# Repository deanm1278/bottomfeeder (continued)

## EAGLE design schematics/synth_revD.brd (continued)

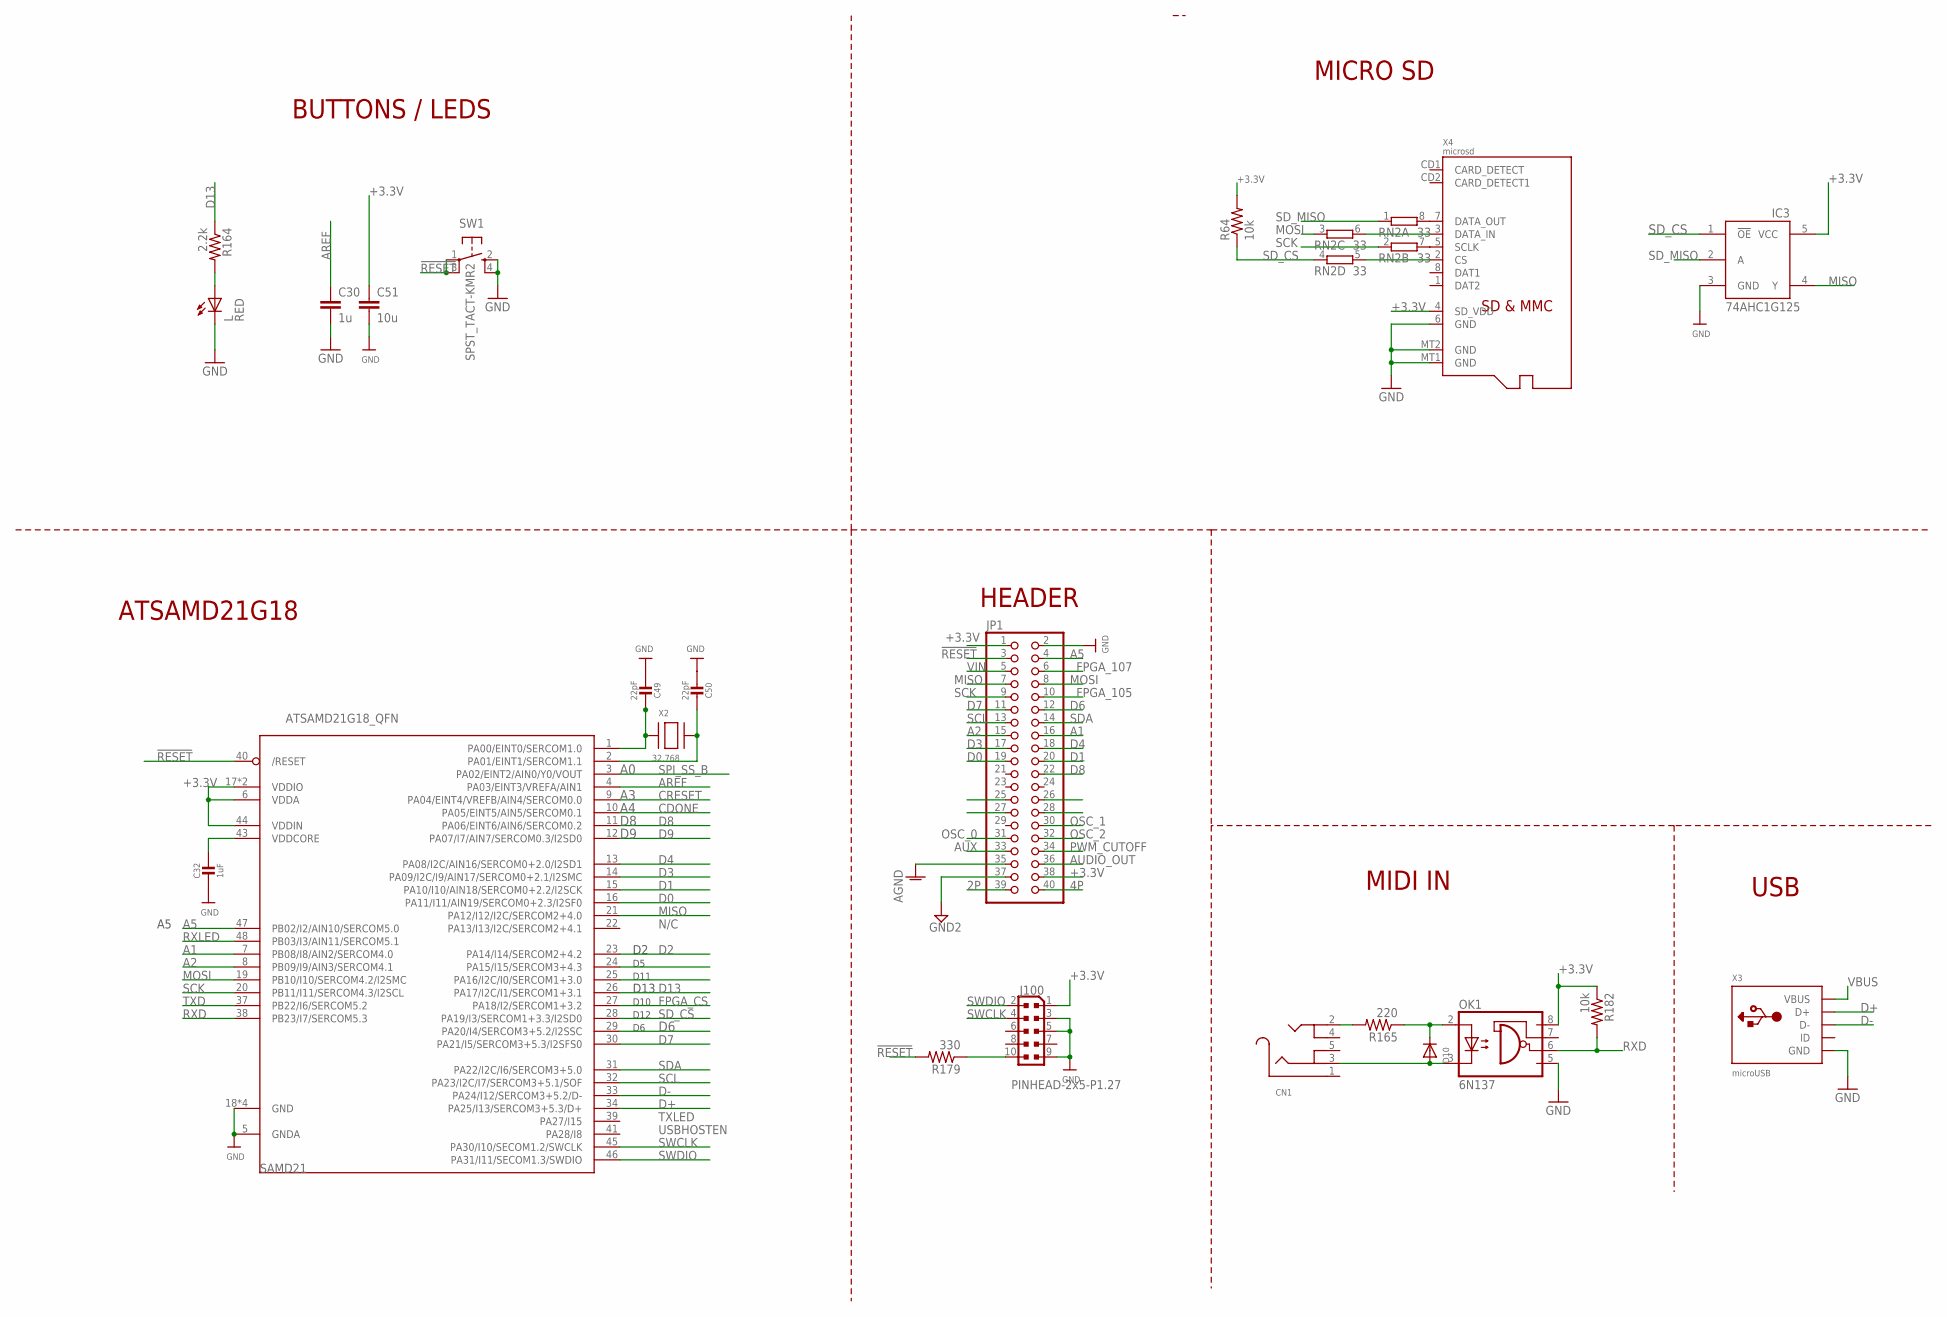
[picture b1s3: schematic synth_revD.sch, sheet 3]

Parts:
C30: 1u; C0603
C32: 1uF; 0603-NO
C49, C50: 22pF; 0603-NO
C51: 10u; C0603
CN1: AUDIO_3.5MMJACK; 4UCONN_19269
D10: DIODESOD-523; SOD-523
IC3: 74AHC1G125; SOT23-5L
J100: PINHEAD-2x5-P1.27; PINHEAD_2X05_127
JP1: PINHD-2X20; 2X20
L: RED; CHIP-LED0805
OK1: 6N137; DIL8-SMD
R64, R182: 10k; R0603
R164: 2.2k; R0603
R165: 220; R0603
R179: 330; R0603
RN2: 33; 0603-ARC
SAMD21: ATSAMD21G18_QFN; TQFN48_7MM
SW1: SPST_TACT-KMR2; KMR2
X2: 32.768; XTAL3215
X3: microUSB; 4UCONN_20329_V2
X4: microsd; MICROSD

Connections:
2P: JP1.39; also elsewhere on the board
4P: JP1.40; also elsewhere on the board
!RESET: JP1.3, R179.2, SAMD21.40 (/RESET), SW1.1, SW1.3 (P1)
+3.3V: C51.1, IC3.5 (VCC), J100.1, JP1.1, JP1.38, OK1.8 (VCC), R64.2, R182.1, SAMD21.6 (VDDA), SAMD21.17 (VDDIO), SAMD21.36 (VDDIO), SAMD21.44 (VDDIN), X4.4 (SD_VDD); also elsewhere on the board
A1: JP1.16, SAMD21.7 (PB08/I8/AIN2/SERCOM4.0)
A2: JP1.15, SAMD21.8 (PB09/I9/AIN3/SERCOM4.1)
A5: JP1.4, SAMD21.47 (PB02/I2/AIN10/SERCOM5.0)
AGND: JP1.35; also elsewhere on the board
AREF: C30.1, SAMD21.4 (PA03/EINT3/VREFA/AIN1)
AUDIO_OUT: JP1.36; also elsewhere on the board
AUX: JP1.33; also elsewhere on the board
CDONE: SAMD21.10 (PA05/EINT5/AIN5/SERCOM0.1); also elsewhere on the board
CRESET: SAMD21.9 (PA04/EINT4/VREFB/AIN4/SERCOM0.0); also elsewhere on the board
D0: JP1.19, SAMD21.16 (PA11/I11/AIN19/SERCOM0+2.3/I2SF0)
D1: JP1.20, SAMD21.15 (PA10/I10/AIN18/SERCOM0+2.2/I2SCK)
D2: SAMD21.23 (PA14/I14/SERCOM2+4.2)
D3: JP1.17, SAMD21.14 (PA09/I2C/I9/AIN17/SERCOM0+2.1/I2SMC)
D4: JP1.18, SAMD21.13 (PA08/I2C/AIN16/SERCOM0+2.0/I2SD1)
D6: JP1.12, SAMD21.29 (PA20/I4/SERCOM3+5.2/I2SSC)
D7: JP1.11, SAMD21.30 (PA21/I5/SERCOM3+5.3/I2SFS0)
D8: JP1.22, SAMD21.11 (PA06/EINT6/AIN6/SERCOM0.2)
D9: SAMD21.12 (PA07/I7/AIN7/SERCOM0.3/I2SD0)
D13: R164.1, SAMD21.26 (PA17/I2C/I1/SERCOM1+3.1)
D+: SAMD21.34 (PA25/I13/SERCOM3+5.3/D+), X3.D+
D-: SAMD21.33 (PA24/I12/SERCOM3+5.2/D-), X3.D-
FPGA_105: JP1.10; also elsewhere on the board
FPGA_107: JP1.6; also elsewhere on the board
FPGA_CS: SAMD21.27 (PA18/I2/SERCOM1+3.2); also elsewhere on the board
GND: C30.2, C32.2, C49.2, C50.2, C51.2, IC3.3 (GND), J100.3, J100.5, J100.9, JP1.2, L.C, OK1.5 (GND), SAMD21.5 (GNDA), SAMD21.18 (GND), SAMD21.35 (GND), SAMD21.42 (GND), SAMD21.THERMAL (GND), SW1.2 (S), SW1.4 (S1), X3.BASE@1 (GND), X3.BASE@2 (GND), X3.GND, X3.SPRT@1 (GND), X3.SPRT@2 (GND), X3.SPRT@3 (GND), X3.SPRT@4 (GND), X4.6 (GND), X4.MT1 (GND), X4.MT2 (GND); also elsewhere on the board
GND2: JP1.37; also elsewhere on the board
MISO: IC3.4 (Y), JP1.7, SAMD21.21 (PA12/I12/I2C/SERCOM2+4.0); also elsewhere on the board
MOSI: JP1.8, RN2.3 (1), SAMD21.19 (PB10/I10/SERCOM4.2/I2SMC); also elsewhere on the board
unnamed: CN1.2, R165.2
unnamed: J100.10, R179.1
unnamed: RN2.8 (2), X4.7 (DATA_OUT)
unnamed: RN2.7 (2), X4.5 (SCLK)
unnamed: RN2.6 (2), X4.3 (DATA_IN)
unnamed: RN2.5 (2), X4.2 (CS)
unnamed: L.A, R164.2
unnamed: C49.1, SAMD21.1 (PA00/EINT0/SERCOM1.0), X2.P$1
unnamed: C50.1, SAMD21.2 (PA01/EINT1/SERCOM1.1), X2.P$2
unnamed: D10.K (C), OK1.2 (A), R165.1
unnamed: CN1.3, D10.A, OK1.3 (C)
OSC_0: JP1.31; also elsewhere on the board
OSC_1: JP1.30; also elsewhere on the board
OSC_2: JP1.32; also elsewhere on the board
PWM_CUTOFF: JP1.34; also elsewhere on the board
RXD: OK1.6 (VO), R182.2, SAMD21.38 (PB23/I7/SERCOM5.3)
RXLED: SAMD21.48 (PB03/I3/AIN11/SERCOM5.1)
SCK: JP1.9, RN2.2 (1), SAMD21.20 (PB11/I11/SERCOM4.3/I2SCL); also elsewhere on the board
SCL: JP1.13, SAMD21.32 (PA23/I2C/I7/SERCOM3+5.1/SOF)
SDA: JP1.14, SAMD21.31 (PA22/I2C/I6/SERCOM3+5.0)
SD_CS: IC3.1 (!OE), R64.1, RN2.4 (1), SAMD21.28 (PA19/I3/SERCOM1+3.3/I2SD0)
SD_MISO: IC3.2 (A), RN2.1
SPI_SS_B: SAMD21.3 (PA02/EINT2/AIN0/Y0/VOUT); also elsewhere on the board
SWCLK: J100.4, SAMD21.45 (PA30/I10/SECOM1.2/SWCLK)
SWDIO: J100.2, SAMD21.46 (PA31/I11/SECOM1.3/SWDIO)
TXD: SAMD21.37 (PB22/I6/SERCOM5.2)
VBUS: X3.VBUS; also elsewhere on the board
VDDCORE1: C32.1, SAMD21.43 (VDDCORE)
VIN: JP1.5; also elsewhere on the board

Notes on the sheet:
N/C
TXLED
USBHOSTEN
RXLED
TXD
RXD
D12
D10
D11
D13
ATSAMD21G18
BUTTONS / LEDS
MICRO SD
USB
HEADER
MIDI IN

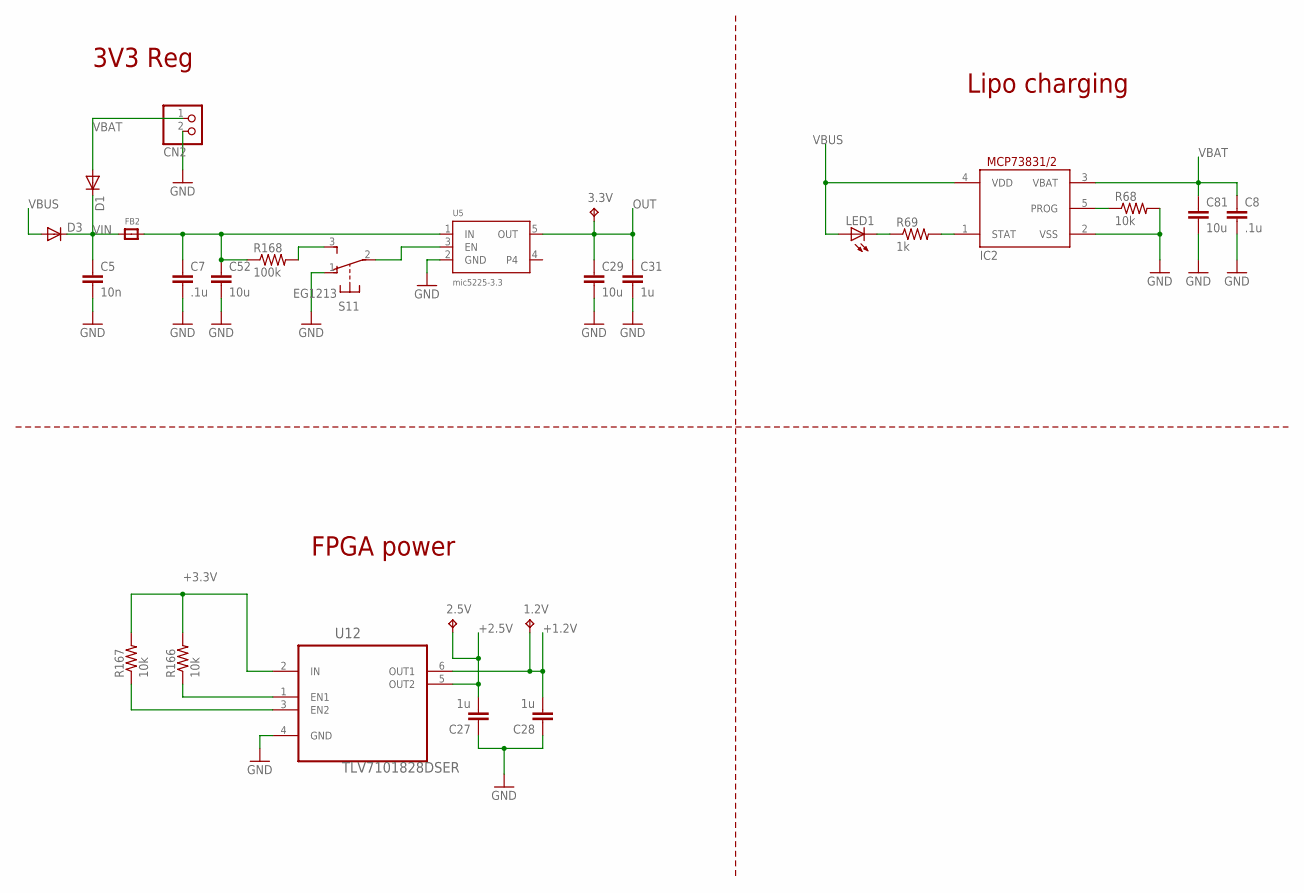
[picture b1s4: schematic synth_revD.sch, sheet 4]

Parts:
1.2V, 2.5V, 3.3V: TPB1,27; B1,27
C5: 10n; C0603
C7, C8: .1u; C0603
C27, C28, C31: 1u; C0603
C29, C52, C81: 10u; C0603
CN2: JST_2PIN-SMT-RA; JST-PH-2-SMT-RA
D1, D3: DIODE-SOD123; SOD123
FB2: FERRITE; 0603
IC2: MCP73831/OT; SOT23-5L
LED1: LEDCHIP-LED0805; CHIP-LED0805
R68, R166, R167: 10k; R0603
R69: 1k; R0603
R168: 100k; R0603
S1: EG1213
U5: mic5225-3.3; SOT23-5
U12: TLV7101828DSER; SON50P150X150X80-6N

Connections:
$P9999: C7.1, C52.1, FB2.2, R168.1, U5.1 (IN)
+1.2V: 1.2V.TP, C28.2, U12.6 (OUT1); also elsewhere on the board
+2.5V: 2.5V.TP, C27.2, U12.5 (OUT2)
+3.3V: R166.2, R167.2, U12.2 (IN); also elsewhere on the board
GND: C5.2, C7.2, C8.2, C27.1, C28.1, C29.2, C31.2, C52.2, C81.2, CN2.2 (1), IC2.2 (VSS), R68.2, S1.1 (O), U5.2 (GND), U12.4 (GND); also elsewhere on the board
unnamed: R168.2, S1.3 (S)
unnamed: IC2.5 (PROG), R68.1
unnamed: S1.2, U5.3 (EN)
unnamed: IC2.1 (STAT), R69.2
unnamed: LED1.C, R69.1
unnamed: R166.1, U12.1 (EN1)
unnamed: R167.1, U12.3 (EN2)
OUT: 3.3V.TP, C29.1, C31.1, U5.5 (OUT)
VBAT: C8.1, C81.1, CN2.1 (2), D1.A, IC2.3 (VBAT)
VBUS: D3.A, IC2.4 (VDD), LED1.A; also elsewhere on the board
VIN: C5.1, D1.C, D3.C, FB2.1; also elsewhere on the board

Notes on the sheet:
FPGA power
3V3 Reg
Lipo charging

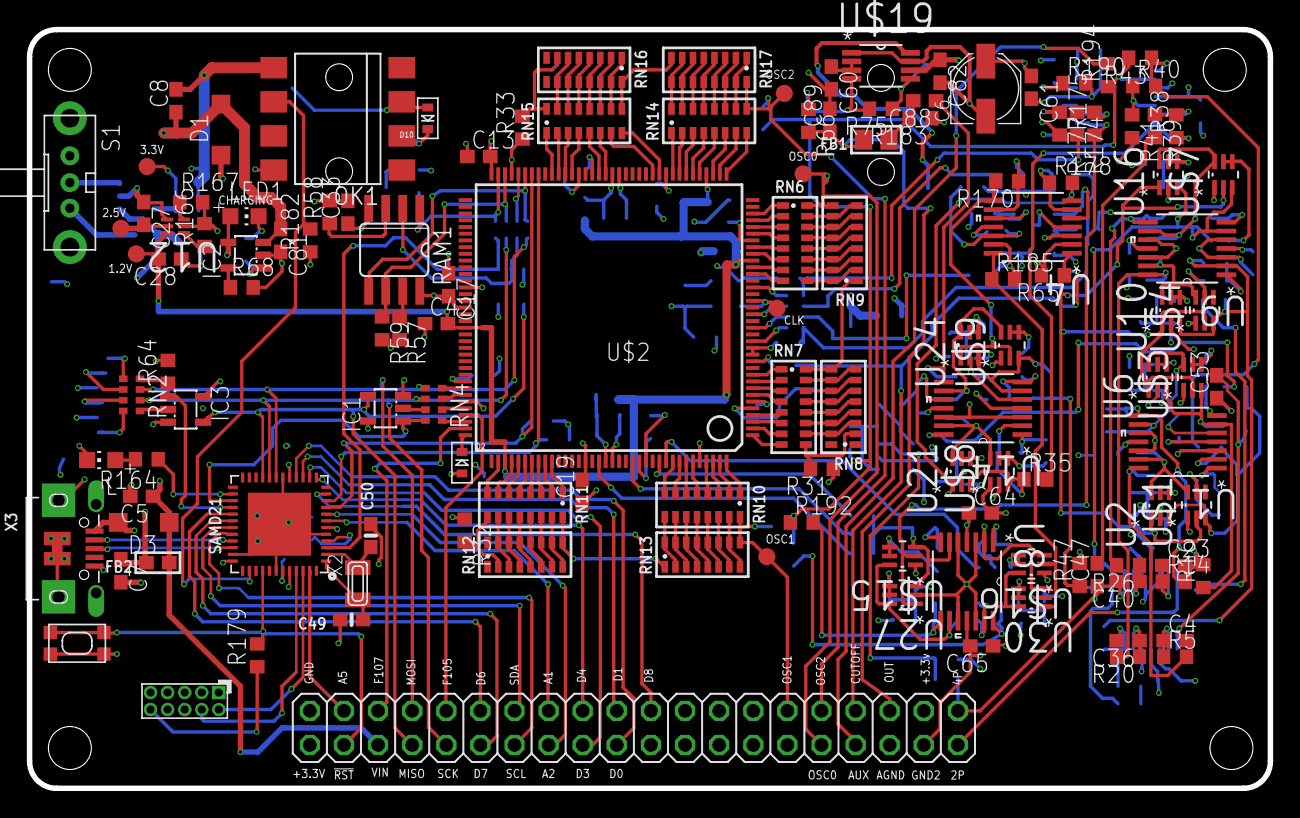
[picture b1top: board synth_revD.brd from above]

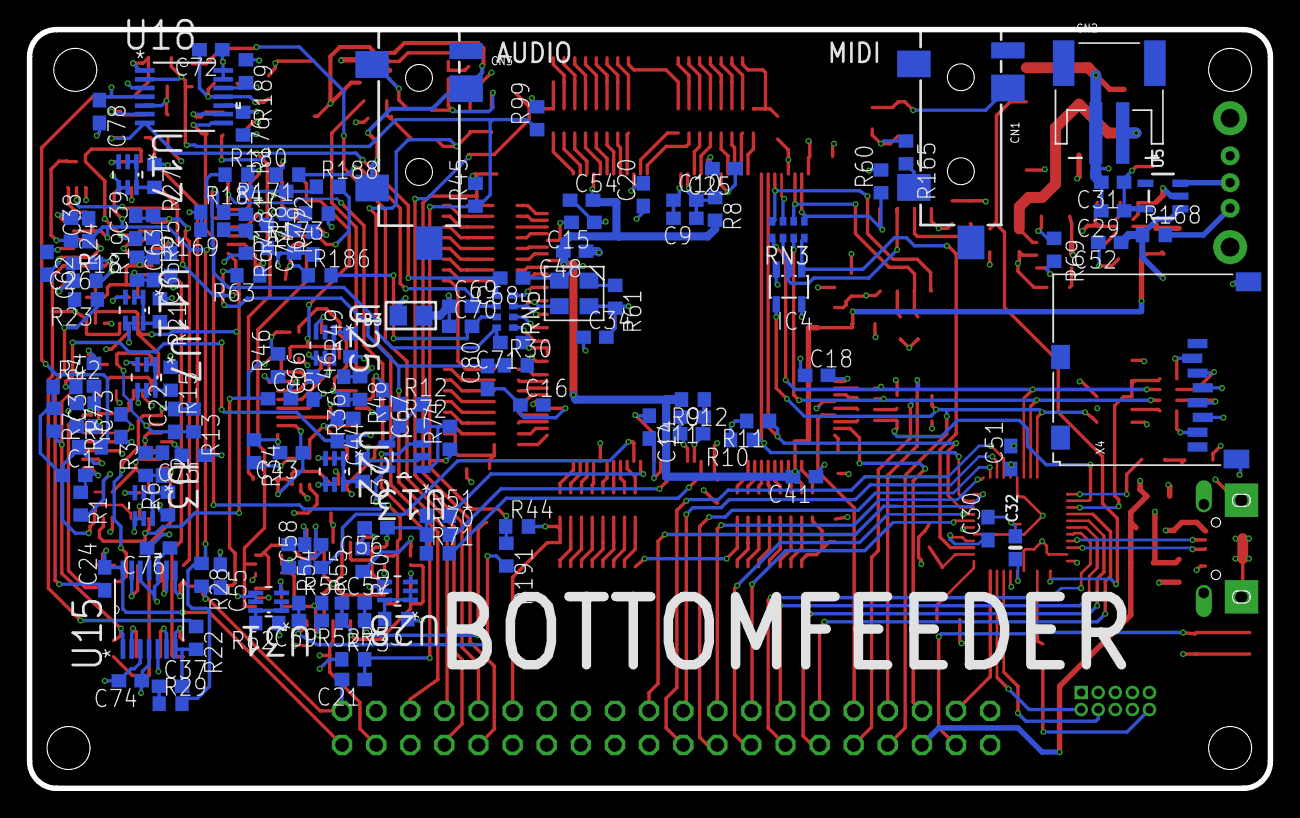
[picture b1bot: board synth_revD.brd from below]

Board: 4 copper layers, 92.4 x 56.5 mm, 276 parts (146 on the bottom side), 290 nets.

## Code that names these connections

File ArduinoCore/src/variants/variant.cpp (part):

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 * +------------+------------------+--------+-----------------+--------------------------------------------------------------------------------------------------------
 * |            | Digital Low      |        |                 |
 * +------------+------------------+--------+-----------------+--------------------------------------------------------------------------------------------------------
 * | 0          | 0 -> RX          |  PA11  |                 | EIC/EXTINT[11] ADC/AIN[19]           PTC/X[3] *SERCOM0/PAD[3]  SERCOM2/PAD[3]  TCC0/WO[3]  TCC1/WO[1]
 * | 1          | 1 <- TX          |  PA10  |                 | EIC/EXTINT[10] ADC/AIN[18]           PTC/X[2] *SERCOM0/PAD[2]                  TCC0/WO[2]  TCC1/WO[0]
 * | 2          | 2                |  PA14  |                 | EIC/EXTINT[14]                                 SERCOM2/PAD[2]  SERCOM4/PAD[2]  TC3/WO[0]   TCC0/WO[4]
 * | 3          | ~3               |  PA09  |                 | EIC/EXTINT[9]  ADC/AIN[17]           PTC/X[1]  SERCOM0/PAD[1]  SERCOM2/PAD[1] *TCC0/WO[1]  TCC1/WO[3]
 * | 4          | ~4               |  PA08  |                 | EIC/NMI        ADC/AIN[16]           PTC/X[0]  SERCOM0/PAD[0]  SERCOM2/PAD[0] *TCC0/WO[0]  TCC1/WO[2]
 * | 5          | ~5               |  PA15  |                 | EIC/EXTINT[15]                                 SERCOM2/PAD[3]  SERCOM4/PAD[3] *TC3/WO[1]   TCC0/WO[5]
 * | 6          | ~6               |  PA20  |                 | EIC/EXTINT[4]                        PTC/X[8]  SERCOM5/PAD[2]  SERCOM3/PAD[2]             *TCC0/WO[6]
 * | 7          | 7                |  PA21  |                 | EIC/EXTINT[5]                        PTC/X[9]  SERCOM5/PAD[3]  SERCOM3/PAD[3]              TCC0/WO[7]
 * +------------+------------------+--------+-----------------+--------------------------------------------------------------------------------------------------------
 * |            | Digital High     |        |                 |
 * +------------+------------------+--------+-----------------+--------------------------------------------------------------------------------------------------------
 * | 8          | ~8               |  PA06  |                 | EIC/EXTINT[6]  ADC/AIN[6]  AC/AIN[2] PTC/Y[4]  SERCOM0/PAD[2]                 *TCC1/WO[0]
 * | 9          | ~9               |  PA07  |                 | EIC/EXTINT[7]  ADC/AIN[7]  AC/AIN[3] PTC/Y[5]  SERCOM0/PAD[3]                 *TCC1/WO[1]
 * | 10         | ~10              |  PA18  |                 | EIC/EXTINT[2]                        PTC/X[6] +SERCOM1/PAD[2]  SERCOM3/PAD[2] *TC3/WO[0]    TCC0/WO[2]
 * | 11         | ~11              |  PA16  |                 | EIC/EXTINT[0]                        PTC/X[4] +SERCOM1/PAD[0]  SERCOM3/PAD[0] *TCC2/WO[0]   TCC0/WO[6]
 * | 12         | ~12              |  PA19  |                 | EIC/EXTINT[3]                        PTC/X[7] +SERCOM1/PAD[3]  SERCOM3/PAD[3]  TC3/WO[1]   *TCC0/WO[3]
 * | 13         | ~13              |  PA17  | LED             | EIC/EXTINT[1]                        PTC/X[5] +SERCOM1/PAD[1]  SERCOM3/PAD[1] *TCC2/WO[1]   TCC0/WO[7]
 * +------------+------------------+--------+-----------------+--------------------------------------------------------------------------------------------------------
 * |            | Analog Connector |        |                 |
 * +------------+------------------+--------+-----------------+--------------------------------------------------------------------------------------------------------
 * | 14         | A0               |  PA02  | A0              | EIC/EXTINT[2] *ADC/AIN[0]  DAC/VOUT  PTC/Y[0]
 * | 15         | A1               |  PB08  | A1              | EIC/EXTINT[8] *ADC/AIN[2]            PTC/Y[14] SERCOM4/PAD[0]                  TC4/WO[0]
 * | 16         | A2               |  PB09  | A2              | EIC/EXTINT[9] *ADC/AIN[3]            PTC/Y[15] SERCOM4/PAD[1]                  TC4/WO[1]
 * | 17         | A3               |  PA04  | A3              | EIC/EXTINT[4] *ADC/AIN[4]  AC/AIN[0] PTC/Y[2]  SERCOM0/PAD[0]                  TCC0/WO[0]
 * | 18         | A4               |  PA05  | A4              | EIC/EXTINT[5] *ADC/AIN[5]  AC/AIN[1] PTC/Y[5]  SERCOM0/PAD[1]                  TCC0/WO[1]
 * | 19         | A5               |  PB02  | A5              | EIC/EXTINT[2] *ADC/AIN[10]           PTC/Y[8]  SERCOM5/PAD[0]
 * +------------+------------------+--------+-----------------+--------------------------------------------------------------------------------------------------------
 * |            | Wire             |        |                 |
 * +------------+------------------+--------+-----------------+--------------------------------------------------------------------------------------------------------
 * | 20         | SDA              |  PA22  | SDA             | EIC/EXTINT[6]                        PTC/X[10] *SERCOM3/PAD[0] SERCOM5/PAD[0] TC4/WO[0] TCC0/WO[4]
 * | 21         | SCL              |  PA23  | SCL             | EIC/EXTINT[7]                        PTC/X[11] *SERCOM3/PAD[1] SERCOM5/PAD[1] TC4/WO[1] TCC0/WO[5]
 * +------------+------------------+--------+-----------------+--------------------------------------------------------------------------------------------------------
 * |            |SPI (Legacy ICSP) |        |                 |
 * +------------+------------------+--------+-----------------+--------------------------------------------------------------------------------------------------------
 * | 22         | 1                |  PA12  | MISO            | EIC/EXTINT[12] SERCOM2/PAD[0] *SERCOM4/PAD[0] TCC2/WO[0] TCC0/WO[6]
 * |            | 2                |        | 5V0             |
 * | 23         | 4                |  PB10  | MOSI            | EIC/EXTINT[10]                *SERCOM4/PAD[2] TC5/WO[0]  TCC0/WO[4]
 * | 24         | 3                |  PB11  | SCK             | EIC/EXTINT[11]                *SERCOM4/PAD[3] TC5/WO[1]  TCC0/WO[5]
 * |            | 5                |        | RESET           |
 * |            | 6                |        | GND             |
 * +------------+------------------+--------+-----------------+--------------------------------------------------------------------------------------------------------
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 * |            | USB              |        |                 |
 * +------------+------------------+--------+-----------------+--------------------------------------------------------------------------------------------------------
 * | 27         |                  |  PA28  | USB_HOST_ENABLE | EIC/EXTINT[8]
 * | 28         |                  |  PA24  | USB_NEGATIVE    | *USB/DM
 * | 29         |                  |  PA25  | USB_POSITIVE    | *USB/DP
 * +------------+------------------+--------+-----------------+--------------------------------------------------------------------------------------------------------
 * |            | EDBG             |        |                 |
 * +------------+------------------+--------+-----------------+--------------------------------------------------------------------------------------------------------
 * | 30         |                  |  PB22  | EDBG_UART TX    | *SERCOM5/PAD[2]
 * | 31         |                  |  PB23  | EDBG_UART RX    | *SERCOM5/PAD[3]
 * +------------+------------------+--------+-----------------+--------------------------------------------------------------------------------------------------------
 * | 32         |                  |  PA22  | EDBG_SDA        | Pin 20 (SDA)
 * | 33         |                  |  PA23  | EDBG_SCL        | Pin 21 (SCL)
 * +------------+------------------+--------+-----------------+--------------------------------------------------------------------------------------------------------
 * | 34         |                  |  PA19  | EDBG_MISO       | EIC/EXTINT[3] *SERCOM1/PAD[3] SERCOM3/PAD[3] TC3/WO[1]  TCC0/WO[3]
 * | 35         |                  |  PA16  | EDBG_MOSI       | EIC/EXTINT[0] *SERCOM1/PAD[0] SERCOM3/PAD[0] TCC2/WO[0] TCC0/WO[6]
 * | 36         |                  |  PA18  | EDBG_SS         | EIC/EXTINT[2] *SERCOM1/PAD[2] SERCOM3/PAD[2] TC3/WO[0]  TCC0/WO[2]
 * | 37         |                  |  PA17  | EDBG_SCK        | EIC/EXTINT[1] *SERCOM1/PAD[1] SERCOM3/PAD[1] TCC2/WO[1] TCC0/WO[7]
 * +------------+------------------+--------+-----------------+--------------------------------------------------------------------------------------------------------
 * | 38         | ATN              |  PA13  | EDBG_GPIO0      | EIC/EXTINT[13] SERCOM2/PAD[1] SERCOM4/PAD[1] *TCC2/WO[1] TCC0/WO[7]
 * | 39         |                  |  PA21  | EDBG_GPIO1      | Pin 7
 * | 40         |                  |  PA06  | EDBG_GPIO2      | Pin 8
 * | 41         |                  |  PA07  | EDBG_GPIO3      | Pin 9
 * +------------+------------------+--------+-----------------+--------------------------------------------------------------------------------------------------------
 * |            |                  |        |                 |
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
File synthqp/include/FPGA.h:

#ifndef LIB_FPGA_H_
#define LIB_FPGA_H_

#include <inttypes.h>
#include "qpcpp.h"
#include "qp_extras.h"
#include "Arduino.h"
#include "SPI.h"

#include "buffer.h"
#include "hsm_id.h"

#define CRESET_B        A3
#define CDONE           A4

#define FPGA_CS			10

#define FPGA_CLKFREQ 150000000
#define FPGA_N 1024

#define DATA_LENGTH (4096)

#define FPGA_REG_MASK(reg) (reg & 0xFF) << 6

#define FPGA_W0_FREQ 0x00
#define FPGA_W1_FREQ 0x01
#define FPGA_W2_FREQ 0x02

#define FPGA_PWM0 0x03 //cutoff
#define FPGA_PWM1 0x04 //reso
#define FPGA_PWM2 0x05 //noise
#define FPGA_PWM3 0x06 //vca
#define FPGA_PWM4 0x07 //sub

#define FPGA_VOL 0x08
#define FPGA_ENABLE 0x09

#define FPGA_A_INTERVAL_HIGH 0x0a
#define FPGA_A_INTERVAL_LOW 0x0b
#define FPGA_D_INTERVAL_HIGH 0x0c
#define FPGA_D_INTERVAL_LOW 0x0d
#define FPGA_R_INTERVAL_HIGH 0x0e
#define FPGA_R_INTERVAL_LOW 0x0f
#define FPGA_SUS_LEVEL 0x10
#define FPGA_ENV0_PWM0_MUL 0x11
#define FPGA_ENV0_PWM2_MUL 0x12

#define FPGA_PORT		0x13

#define FPGA_KEY_PRESSED 0x14

#define FPGA_SUB_OFF 0x00
#define FPGA_SUB0 0x01
#define FPGA_SUB1 0x02
#define FPGA_SUB2 0x04

#define FPGA_RW_BIT(bit) (bit << 15)

#define FPGA_VOL_MASK(num)	(0x7 << (uint16_t)(3 * (num - 1)))
#define FPGA_VOL_BITS(num, vol)	((vol & 0x7) << (uint16_t)(3 * (num - 1)))

#define FPGA_WRITE_ENABLE_MASK	0x70
#define FPGA_WRITE_ENABLE_CHANNEL(num) (1 << (num + 4))
#define FPGA_WRITE_ENABLE_BIT	0x80

#define FPGA_KEY_PRESSED_BIT 0x100

using namespace QP;
using namespace FW;

class FPGA : public QActive {
	
public:
	FPGA();
	~FPGA();
	
	void Start(uint8_t prio);
	
	protected:
	static QState InitialPseudoState(FPGA * const me, QEvt const * const e);
	static QState Root(FPGA * const me, QEvt const * const e);
	static QState Stopped(FPGA * const me, QEvt const * const e);
	static QState Started(FPGA * const me, QEvt const * const e);
	static QState WritingWave(FPGA * const me, QEvt const * const e);
	
	enum {
		EVT_QUEUE_COUNT = 32,
		DEFER_QUEUE_COUNT = 16
	};
	QEvt const *m_evtQueueStor[EVT_QUEUE_COUNT];
	QEvt const *m_deferQueueStor[DEFER_QUEUE_COUNT];
	QEQueue m_deferQueue;
	uint8_t m_id;
	char const * m_name;
	
private:

	void writeReg(uint8_t reg, uint16_t value);
	uint16_t readReg(uint8_t reg);
	
	SPISettings settings;
	
	//for writing waves
	uint8_t writeChannel;
	uint8_t writeNum;
	
	QTimeEvt m_startTimer;
};

#endif

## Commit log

2017-05-20 cleanup, docs, bugfixes
2017-05-23 added saving and loading presets, fixed bugs
2017-05-25 about to f some stuff up... quicksaving
2017-05-28 read from flash instead
2017-05-29 read waves from flash instead of sd card
2017-06-05 fixes and stuff
2017-06-13 removed captouch, fixed some bugs, fixed reso scaling
2017-07-25 DM: not sure
2017-09-16 updates and fixes
2017-09-16 added missing stuff
2017-09-16 updated image Please enter the commit message for your changes. Lines starting
2018-07-01 add pdf schematic and update readme
